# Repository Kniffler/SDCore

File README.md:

# SDCore
So I went and made an entire SD card because I thought my PicoCalc didn't have enough juice.

## IMPORTANT (READ THIS)
Please read through the entire README in order to get a grasp of the limitations of this project since they might save your skin while developing.

TL;DR: [Restrictions summary](#restrictions-summary)

### Also important
I am not responsible for your usage or misusage of this project.

## Specs
This SD core is based on the RP2350A by raspberry pi and features:
- Hardware-level control of the routing of the SD pins
- 3 state-indicating LEDs (power, program, and select)
- 16MiB of flash
- A micro-SD card slot
- Additional GPIO output (see below)
- An access point for USB programming when setting pin 6 to 3.3V

Annoyingly, when using the edge connector and the micro-SD card slot at the same time, no SPI interface will be left to use on the device, nor will the corresponding pins (see [pinout](#pinout)) be available for anything else.

# Images
None yet, we'll see when the order arrives.

# Hardware pin control
I added a tri-state demultiplexer ([NMUX27518EPWJ](https://assets.nexperia.com/documents/data-sheet/NMUX27518E.pdf)) to switch between 2 modes, direct transfer mode and sniffing mode (default is direct transfer mode). In direct transfer mode, the data0-data3, CLK and CMD pins from the edge connector are all mapped to the RP2350A and set up for communication via **SPI1**. While sniffing mode also maps the edge connector to the MCU, it does so via **SPI0** and also directs them towards the micro-SD card slot allowing the MCU to sniff/spy on the communication between the host device and the micro-SD card.

> [!IMPORTANT]
> When using direct transfer mode, SPI1 is used and in sniffing mode we use SPI0. The pinouts are inherently different. Please look at the [pinout](#pinout) section for details.

The different SPI controllers are utilized in order to communicate with the host and the micro-SD card separately and/or simultaneously.

# How to program the RP2350A
There are 2 main scenarios, either you have the programmer board, or you don't. In the case that you do, connect the USB-C port to your PC or laptop, plug the SD core into the programmer board while holding the button on the board, once you see the USB mass storage on your PC (which you have presumably plugged into the programmer board already) you can release the button.

If you do not own a programmer board, (though it is highly recommended that you do) you can order one with the given gerber, BOM and P&P files which can be found in the `SDCore_progBoard/prodution` folder which also holds a few key values for ordering with PCB Assembly on [JLCPCB](jlcpcb.com).

> [!NOTE]
> The `.zip` file is the compressed gerber files, `bom.csv` is the BOM and `positions.csv` is the P&P file.

If ordering this PCB is not an option, please continue in the subsection below.

## Making a programmer board at home
You'll need:
- A reliable 3.3V power source
- A switch
- A breakout board of any USB end (male or female, type-A or type-C, whichever you can use to plug into your PC) with a D- and a D+ pin. If there are multiple of each, short them such that you only have **one** D- and **one** D+
- A breakout board of a **standard SD card** with ALL of these pins present: 3 (VSS/GND), 4 (VDD/3V3), 6 (the magic pin), 8 (DAT1) and 9 (DAT2) - other pins are optional

> [!WARNING]
> If any of these SD pins are missing from the breakout, you will not be able to program your SDCore.

If you don't have an SD breakout, look have a look at [this](https://www.instructables.com/Cheap-DIY-SD-card-breadboard-socket/) article on how to make one with all the needed pins.

Now you connect it as follows (the pins refer to the SD breakout board):
1. GND to pin 3 (may also be labeled as VSS or GND)
2. 3.3V to pin 4 (may also be labeled as VDD, VCC or 3V3)
3. USB D- (data negative/minus) to pin 8 (may also be labeled as DATA1 or DAT1)
4. USB D+ (data negative/minus) to pin 9 (may also be labeled as DATA2 or DAT2)
5. Connect one end of the switch to 3.3V and the other to pin 6 (may also be labeled as VSS or GND)

You may leave all the other pins unconnected or tie them to GND.

Normally, pin 6 is an alternate GND pin, however the SD core uses it to signify the BOOTSEL function and boot into the USB mass storage bootloader. 
> [!WARNING]
> Using this setup for a regular SD card will lead to shorts when pressing the switch.

> [!CAUTION]
> This device does not support booting via UART, USB is currently the only supported boot form.

You can now plug this setup into your PC, enable the 3.3V source and connect the SD core while holding the switch. Once you see a USB mass storage device you may release the switch.

# Pinout
By default, the SD pins are configured to go to the MCU directly over the following pins:
```
Using SPI1
GPIO 8 - SPI1 MISO
GPIO 9 - SPI1 CSn
GPIO 10 - SPI1 CLK
GPIO 11 - SPI1 MOSI

GPIO 0 - DATA1 (pin 8)
GPIO 1 - DATA2 (pin 9)
```
in sniffing mode, they connect as follows:
```
Using SPI0
GPIO 4 - SPI0 MISO
GPIO 5 - SPI0 CSn
GPIO 6 - SPI0 CLK
GPIO 7 - SPI0 MOSI

GPIO 24 - DATA1 (pin 8)
GPIO 25 - DATA2 (pin 9)
```

The selection signal is controlled by GPIO 3 and is pulled down to GND with 10kΩ. Driving this signal high will put the demultiplexer into the sniffing mode pinout, whereas the direct mode's pinout becomes disconnected.

The connections/pins 3V3, GND, SWCLK, SWDIO, RUN, GPIO 2, GPIO 12-23 and GPIO 26-29 are exposed via a board-to-board connector on the SDCore. A breakout cable has not yet been added to this repo.

> [!CAUTION]
> The USB signals of the RP2350A are always connected to the DATA 1 and 2 pins.
> It is the user's responsibility to ensure the MCU does not read USB when it is not supposed to, this also means disabling stdio over USB ***and*** stdio over UART when not using the programmer board.

# Restrictions summary
1. The SD core takes up all of the SPI interfaces in certain use cases - avoid using SPI interfaces via the exposed GPIO pins
2. The SPI interface changes based on the state of the demultiplexer - switch SPI interface and pins when toggling GPIO 3
3. USB is always conntected to data pins 1 and 2, as such it may also be connected to GPIO pairs 24/25 or 0/1 - never use USB when the active GPIO pair may interfere
4. UART bootloader is inaccessible - only program via USB or custom software
5. Pin 6 is usually tied to ground by SD slots, meaning ground will only go through pin 3 - be sure to keep the current low to avoid burnout
6. The switch on the programmer board/circuit may not be pressed while a regular SD card is plugged in - avoid using the programmer board/circuit with regular SD cards
7. Power draw is severly limited due to the SD pad contact area - avoid powering more GPIOs than absolutely necessary or use an external 3.3V source for any additions (e.g. sensors)
8. ***Absolutely no overclocking***. Due to the power limits, drawing more than the slot allows may lead to melting of the contact pins and ruin your programmer board/circuit.

# Credits
All mine baby.

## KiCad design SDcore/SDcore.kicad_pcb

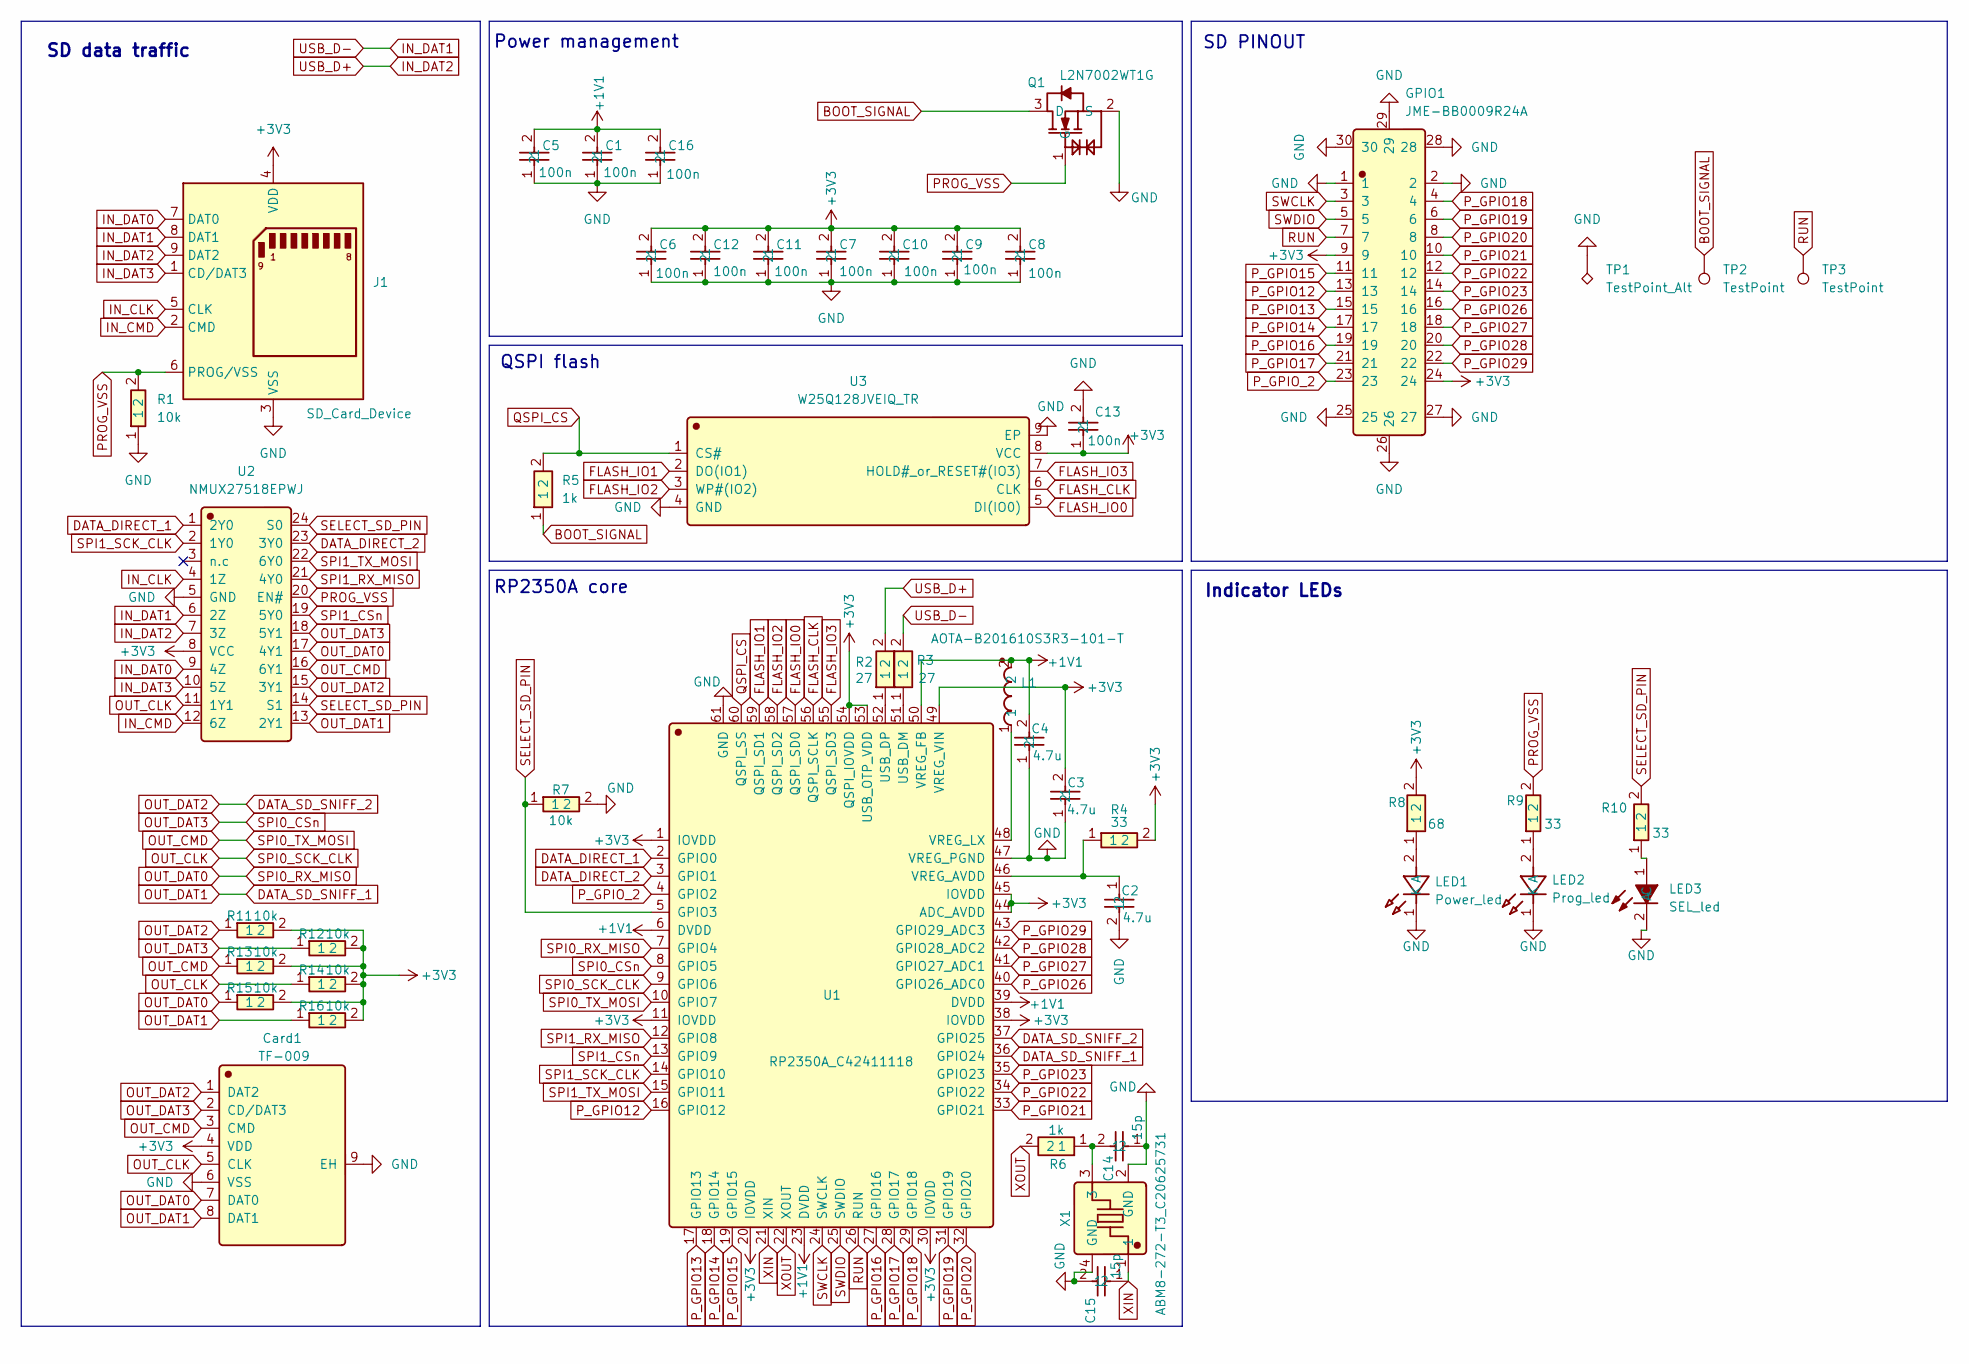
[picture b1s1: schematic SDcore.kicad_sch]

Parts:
C1, C5, C6, C7, C8, C9, C10, C11, C12, C13, C16: 100n; 0402B104K250NT; Manufacturer Part 0402B104K250NT; LCSC C56392
C2, C3, C4: 4.7u; C1005X5R0J475MTJ00E; Manufacturer Part C1005X5R0J475MTJ00E; LCSC C23687
C14, C15: 15p; 0402CG150J500NT; Manufacturer Part 0402CG150J500NT; LCSC C1548
Card1: TF-009; Manufacturer Part TF-009; LCSC C428466
GPIO1: JME-BB0009R24A; Manufacturer Part JME-BB0009R24A; LCSC C50087608
J1: SD_Card_Device; SD_Card_Device_16mm_SlotDepth
L1: AOTA-B201610S3R3-101-T; Manufacturer Part AOTA-B201610S3R3-101-T; LCSC C42411119
LED1: Power_led; XL-1005SURC_C25503345; Manufacturer Part XL-1005SURC; LCSC C25503345
LED2: Prog_led; XL-1005UBC_C22355736; Manufacturer Part XL-1005UBC; LCSC C22355736
LED3: SEL_led; 16-213_GHC-YR1S1_3T; Manufacturer Part 16-213/GHC-YR1S1/3T; LCSC C74338
Q1: L2N7002WT1G; Manufacturer Part L2N7002WT1G; LCSC C12778
R1, R7, R11, R12, R13, R14, R15, R16: 10k; CRCW040210K0FKED; Manufacturer Part CRCW040210K0FKED; LCSC C71617
R2, R3: 27; RT0402BRD0727RL; Manufacturer Part RT0402BRD0727RL; LCSC C852682
R4, R9, R10: 33; CRCW040233R0FKED; Manufacturer Part CRCW040233R0FKED; LCSC C242490
R5, R6: 1k; CRCW04021K00FKED; Manufacturer Part CRCW04021K00FKED; LCSC C71623
R8: 68; ERJPA2F68R0X; Manufacturer Part ERJPA2F68R0X; LCSC C542959
TP1: TestPoint_Alt; TestPoint_Pad_1.0x1.0mm
TP2, TP3: TestPoint; TestPoint_Pad_D1.0mm
U1: RP2350A_C42411118; Manufacturer Part RP2350A; LCSC C42411118
U2: NMUX27518EPWJ; Manufacturer Part NMUX27518EPWJ; LCSC C50341769
U3: W25Q128JVEIQ_TR; Manufacturer Part W25Q128JVEIQ TR; LCSC C2456297
X1: ABM8-272-T3_C20625731; Manufacturer Part ABM8-272-T3; LCSC C20625731

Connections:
+1V1: C1.2, C4.2, C5.2, C16.2, L1.2, U1.6 (DVDD), U1.23 (DVDD), U1.39 (DVDD), U1.50 (VREG_FB)
+3V3: C3.2, C6.2, C7.2, C8.2, C9.2, C10.2, C11.2, C12.2, C13.1, Card1.4 (VDD), GPIO1.9, GPIO1.24, J1.4 (VDD), R4.2, R8.2, R11.2, R12.2, R13.2, R14.2, R15.2, R16.2, U1.1 (IOVDD), U1.11 (IOVDD), U1.20 (IOVDD), U1.30 (IOVDD), U1.38 (IOVDD), U1.44 (ADC_AVDD), U1.45 (IOVDD), U1.49 (VREG_VIN), U1.53 (USB_OTP_VDD), U1.54 (QSPI_IOVDD), U2.8 (VCC), U3.8 (VCC)
BOOT_SIGNAL: Q1.3 (D), R5.1, TP2.1
DATA_DIRECT_1: U1.2 (GPIO0), U2.1 (2Y0)
DATA_DIRECT_2: U1.3 (GPIO1), U2.23 (3Y0)
DATA_SD_SNIFF_1: Card1.8 (DAT1), R16.1, U1.36 (GPIO24), U2.13 (2Y1)
DATA_SD_SNIFF_2: Card1.1 (DAT2), R11.1, U1.37 (GPIO25), U2.15 (3Y1)
FLASH_CLK: U1.56 (QSPI_SCLK), U3.6 (CLK)
FLASH_IO0: U1.57 (QSPI_SD0), U3.5 (DI(IO0))
FLASH_IO1: U1.59 (QSPI_SD1), U3.2 (DO(IO1))
FLASH_IO2: U1.58 (QSPI_SD2), U3.3 (WP#(IO2))
FLASH_IO3: U1.55 (QSPI_SD3), U3.7 (HOLD#_or_RESET#(IO3))
GND: C1.1, C2.2, C3.1, C4.1, C5.1, C6.1, C7.1, C8.1, C9.1, C10.1, C11.1, C12.1, C13.2, C14.1, C15.2, C16.1, Card1.6 (VSS), Card1.9 (EH), GPIO1.1, GPIO1.2, GPIO1.25, GPIO1.26, GPIO1.27, GPIO1.28, GPIO1.29, GPIO1.30, J1.3 (VSS), LED1.1 (K), LED2.1 (K), LED3.2 (C), Q1.2 (S), R1.1, R7.2, TP1.1, U1.47 (VREG_PGND), U1.61 (GND), U2.5 (GND), U3.4 (GND), U3.9 (EP), X1.2 (GND), X1.4 (GND)
IN_CLK: J1.5 (CLK), U2.4 (1Z)
IN_CMD: J1.2 (CMD), U2.12 (6Z)
IN_DAT0: J1.7 (DAT0), U2.9 (4Z)
IN_DAT1: J1.8 (DAT1), R3.2, U2.6 (2Z)
IN_DAT2: J1.9 (DAT2), R2.2, U2.7 (3Z)
IN_DAT3: J1.1 (CD/DAT3), U2.10 (5Z)
unnamed: C14.2, R6.1, X1.3
unnamed: LED1.2 (A), R8.1
unnamed: LED2.2 (A), R9.1
unnamed: LED3.1 (A), R10.1
unnamed: R3.1, U1.51 (USB_DM)
unnamed: R2.1, U1.52 (USB_DP)
unnamed: C2.1, R4.1, U1.46 (VREG_AVDD)
unnamed: L1.1, U1.48 (VREG_LX)
OUT_CLK: Card1.5 (CLK), R14.1, U1.9 (GPIO6), U2.11 (1Y1)
OUT_CMD: Card1.3 (CMD), R13.1, U1.10 (GPIO7), U2.16 (6Y1)
OUT_DAT0: Card1.7 (DAT0), R15.1, U1.7 (GPIO4), U2.17 (4Y1)
OUT_DAT3: Card1.2 (CD/DAT3), R12.1, U1.8 (GPIO5), U2.18 (5Y1)
PROG_VSS: J1.6 (PROG/VSS), Q1.1 (G), R1.2, R9.2, U2.20 (EN#)
P_GPIO12: GPIO1.13, U1.16 (GPIO12)
P_GPIO13: GPIO1.15, U1.17 (GPIO13)
P_GPIO14: GPIO1.17, U1.18 (GPIO14)
P_GPIO15: GPIO1.11, U1.19 (GPIO15)
P_GPIO16: GPIO1.19, U1.27 (GPIO16)
P_GPIO17: GPIO1.21, U1.28 (GPIO17)
P_GPIO18: GPIO1.4, U1.29 (GPIO18)
P_GPIO19: GPIO1.6, U1.31 (GPIO19)
P_GPIO20: GPIO1.8, U1.32 (GPIO20)
P_GPIO21: GPIO1.10, U1.33 (GPIO21)
P_GPIO22: GPIO1.12, U1.34 (GPIO22)
P_GPIO23: GPIO1.14, U1.35 (GPIO23)
P_GPIO26: GPIO1.16, U1.40 (GPIO26_ADC0)
P_GPIO27: GPIO1.18, U1.41 (GPIO27_ADC1)
P_GPIO28: GPIO1.20, U1.42 (GPIO28_ADC2)
P_GPIO29: GPIO1.22, U1.43 (GPIO29_ADC3)
P_GPIO_2: GPIO1.23, U1.4 (GPIO2)
QSPI_CS: R5.2, U1.60 (QSPI_SS), U3.1 (CS#)
RUN: GPIO1.7, TP3.1, U1.26 (RUN)
SELECT_SD_PIN: R7.1, R10.2, U1.5 (GPIO3), U2.14 (S1), U2.24 (S0)
SPI1_CSn: U1.13 (GPIO9), U2.19 (5Y0)
SPI1_RX_MISO: U1.12 (GPIO8), U2.21 (4Y0)
SPI1_SCK_CLK: U1.14 (GPIO10), U2.2 (1Y0)
SPI1_TX_MOSI: U1.15 (GPIO11), U2.22 (6Y0)
SWCLK: GPIO1.3, U1.24 (SWCLK)
SWDIO: GPIO1.5, U1.25 (SWDIO)
XIN: C15.1, U1.21 (XIN), X1.1
XOUT: R6.2, U1.22 (XOUT)

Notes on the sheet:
Indicator LEDs
SD PINOUT
SD data traffic
Power management
RP2350A core
QSPI flash

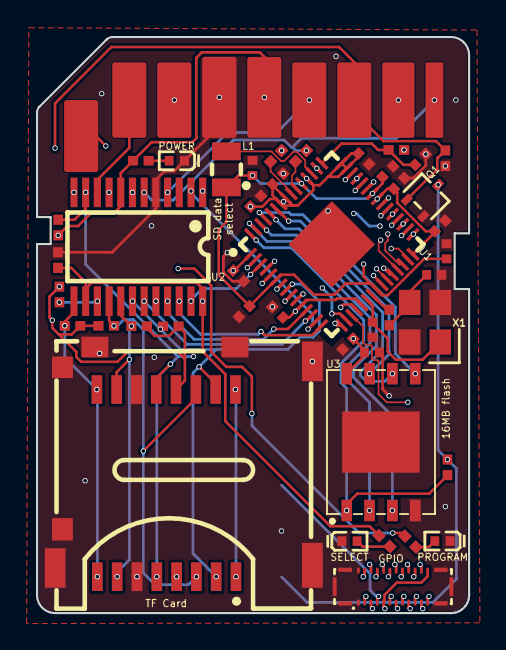
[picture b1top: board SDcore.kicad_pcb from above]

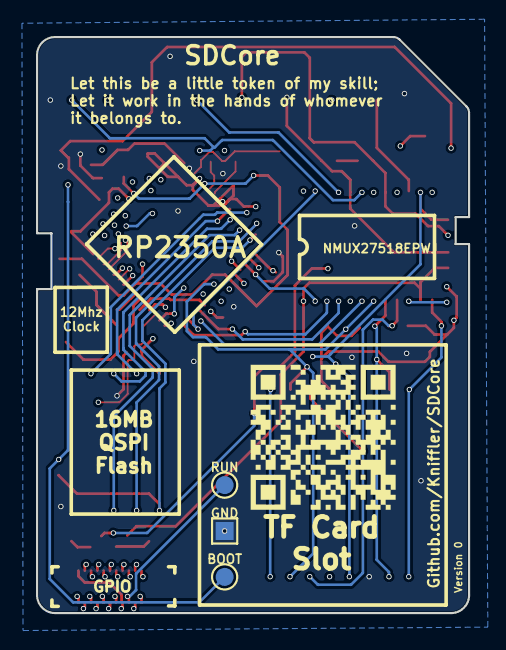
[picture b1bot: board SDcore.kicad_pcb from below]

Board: 4 copper layers, 24.0 x 32.0 mm, 47 parts (3 on the bottom side), 60 nets.

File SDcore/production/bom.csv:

Designator,Footprint,Quantity,Value,LCSC Part #
"C1, C10, C11, C12, C13, C16, C5, C6, C7, C8, C9",0402B104K250NT,11,100n,C56392
"C14, C15",0402CG150J500NT,2,15p,C1548
"C2, C3, C4",C1005X5R0J475MTJ00E,3,4.7u,C23687
CARD1,TF-009,1,TF-009,C428466
GPIO1,JME-BB0009R24A,1,JME-BB0009R24A,C50087608
J1,SD_Card_Device_16mm_SlotDepth,1,SD_Card_Device,
L1,AOTA-B201610S3R3-101-T,1,~,C42411119
LED1,XL-1005SURC_C25503345,1,Power_led,C25503345
LED2,XL-1005UBC_C22355736,1,Prog_led,C22355736
LED3,16-213_GHC-YR1S1_3T,1,SEL_led,C74338
Q1,L2N7002WT1G,1,~,C12778
"R1, R11, R12, R13, R14, R15, R16, R7",CRCW040210K0FKED,8,10k,C71617
"R10, R4, R9",CRCW040233R0FKED,3,33,C242490
"R2, R3",RT0402BRD0727RL,2,27,C852682
"R5, R6",CRCW04021K00FKED,2,1k,C71623
R8,ERJPA2F68R0X,1,68,C542959
U1,RP2350A_C42411118,1,RP2350A_C42411118,C42411118
U2,NMUX27518EPWJ,1,NMUX27518EPWJ,C50341769
U3,W25Q128JVEIQ_TR,1,W25Q128JVEIQ_TR,C2456297
X1,ABM8-272-T3_C20625731,1,ABM8-272-T3_C20625731,C20625731

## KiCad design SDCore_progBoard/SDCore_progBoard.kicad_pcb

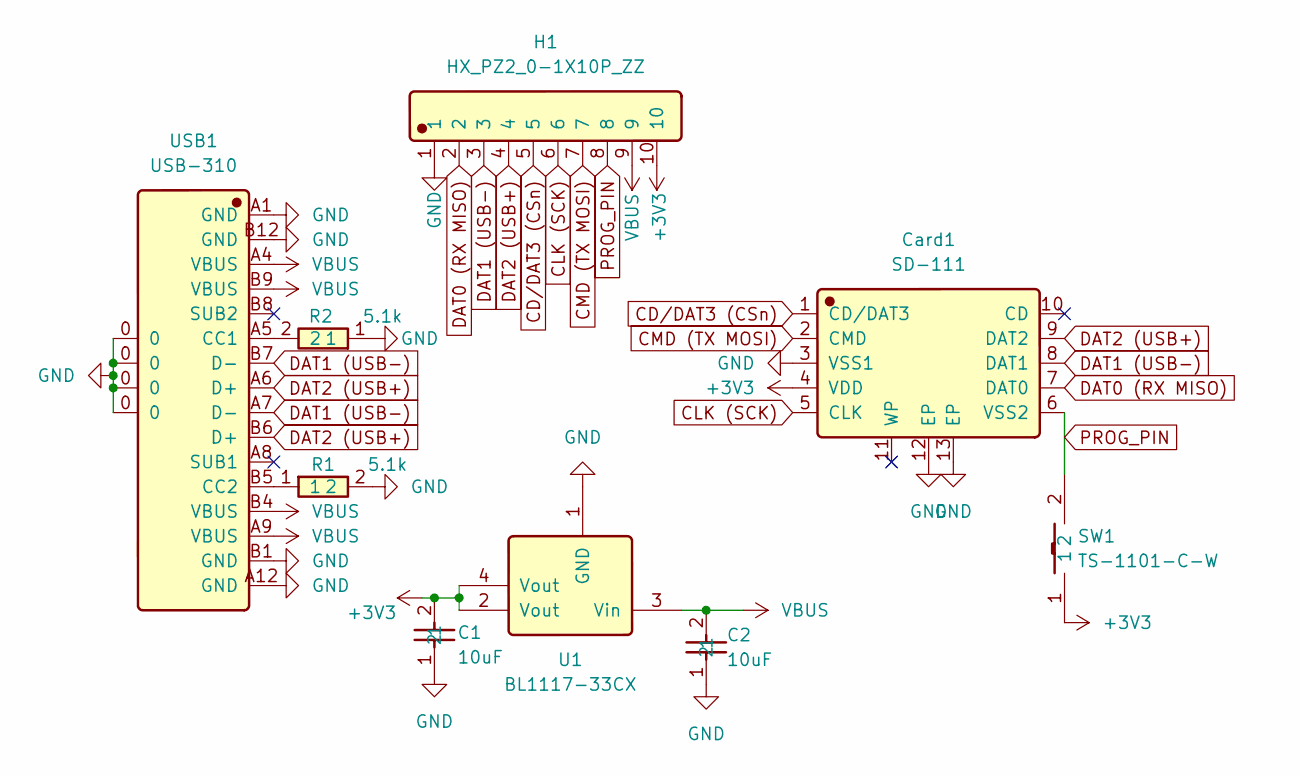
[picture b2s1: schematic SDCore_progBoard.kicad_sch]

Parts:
C1, C2: 10uF; CL05A106MQ5NUNC; Manufacturer Part CL05A106MQ5NUNC; LCSC C15525
Card1: SD-111; Manufacturer Part SD-111; LCSC C410353
H1: HX_PZ2_0-1X10P_ZZ; Manufacturer Part HX PZ2.0-1x10P ZZ; LCSC C22438293
R1, R2: 5.1k; 0603WAF5101T5E; Manufacturer Part 0603WAF5101T5E; LCSC C23186
SW1: TS-1101-C-W; Manufacturer Part TS-1101-C-W; LCSC C318938
U1: BL1117-33CX; Manufacturer Part BL1117-33CX; LCSC C5400
USB1: USB-310; Manufacturer Part USB-310-B-SU; LCSC C309347

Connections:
+3V3: C1.2, Card1.4 (VDD), H1.10, SW1.1, U1.2 (Vout), U1.4 (Vout)
CD/DAT3 (CSn): Card1.1 (CD/DAT3), H1.5
CLK (SCK): Card1.5 (CLK), H1.6
CMD (TX MOSI): Card1.2 (CMD), H1.7
DAT0 (RX MISO): Card1.7 (DAT0), H1.2
DAT1 (USB-): Card1.8 (DAT1), H1.3, USB1.A7 (D-), USB1.B7 (D-)
DAT2 (USB+): Card1.9 (DAT2), H1.4, USB1.A6 (D+), USB1.B6 (D+)
GND: C1.1, C2.1, Card1.3 (VSS1), Card1.12 (EP), Card1.13 (EP), H1.1, R1.2, R2.1, U1.1 (GND), USB1.0, USB1.A1 (GND), USB1.A12 (GND), USB1.B1 (GND), USB1.B12 (GND)
unnamed: R2.2, USB1.A5 (CC1)
unnamed: R1.1, USB1.B5 (CC2)
PROG_PIN: Card1.6 (VSS2), H1.8, SW1.2
VBUS: C2.2, H1.9, U1.3 (Vin), USB1.A4 (VBUS), USB1.A9 (VBUS), USB1.B4 (VBUS), USB1.B9 (VBUS)

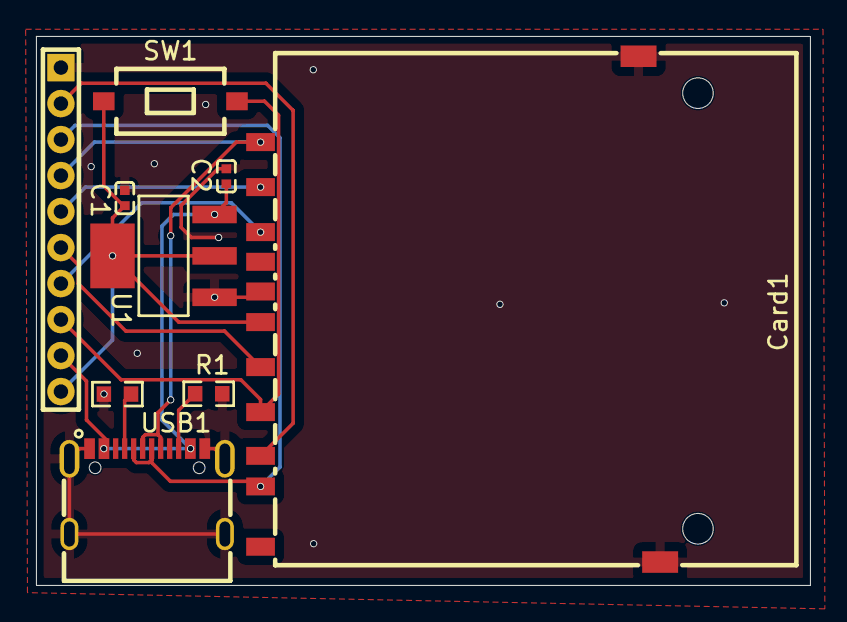
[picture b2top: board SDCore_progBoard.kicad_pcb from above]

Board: 2 copper layers, 43.0 x 30.5 mm, 9 parts (0 on the bottom side), 12 nets.

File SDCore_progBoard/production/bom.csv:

Designator,Footprint,Quantity,Value,LCSC Part #
"C1, C2",CL05A106MQ5NUNC,2,10uF,C15525
CARD1,SD-111,1,SD-111,C410353
H1,HX_PZ2_0-1X10P_ZZ,1,HX_PZ2_0-1X10P_ZZ,C22438293
"R1, R2",0603WAF5101T5E,2,5.1k,C23186
SW1,TS-1101-C-W,1,TS-1101-C-W,C318938
U1,BL1117-33CX,1,BL1117-33CX,C5400
USB1,USB-310,1,USB-310,C309347
